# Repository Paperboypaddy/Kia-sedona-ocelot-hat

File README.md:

# Kia Sedona 2004 Ocelot Hat
The idea of this Ocelot V2 Hat design is to control the stock cruise control system in the car currently as well as adding a K Line Lin Bus tranciever to act like a ELM327 to capture car speed and other stats for openpilot.

Im using a MC33660BEFR2 chip to interface with Lin Bus K-Line over serial USART. USART isconnected to PB10 (TX) and PC5 (RX) on the Ocelot, along with Enable connected to PB1.

As for the cruise control switches and mosfets, my stock cruise control system is using 12v signals for the buttons. The series of mosfets are connected to PC10 (CCSET_INPUT) and PC11 (CCRES_INPUT). And the Stock Switches are connected to 3.3V and PC12 (CCSET_SW) and PD2 (CCRES_SW). 

I've also added a RGB status LED in place where the Black Panda would have had one.

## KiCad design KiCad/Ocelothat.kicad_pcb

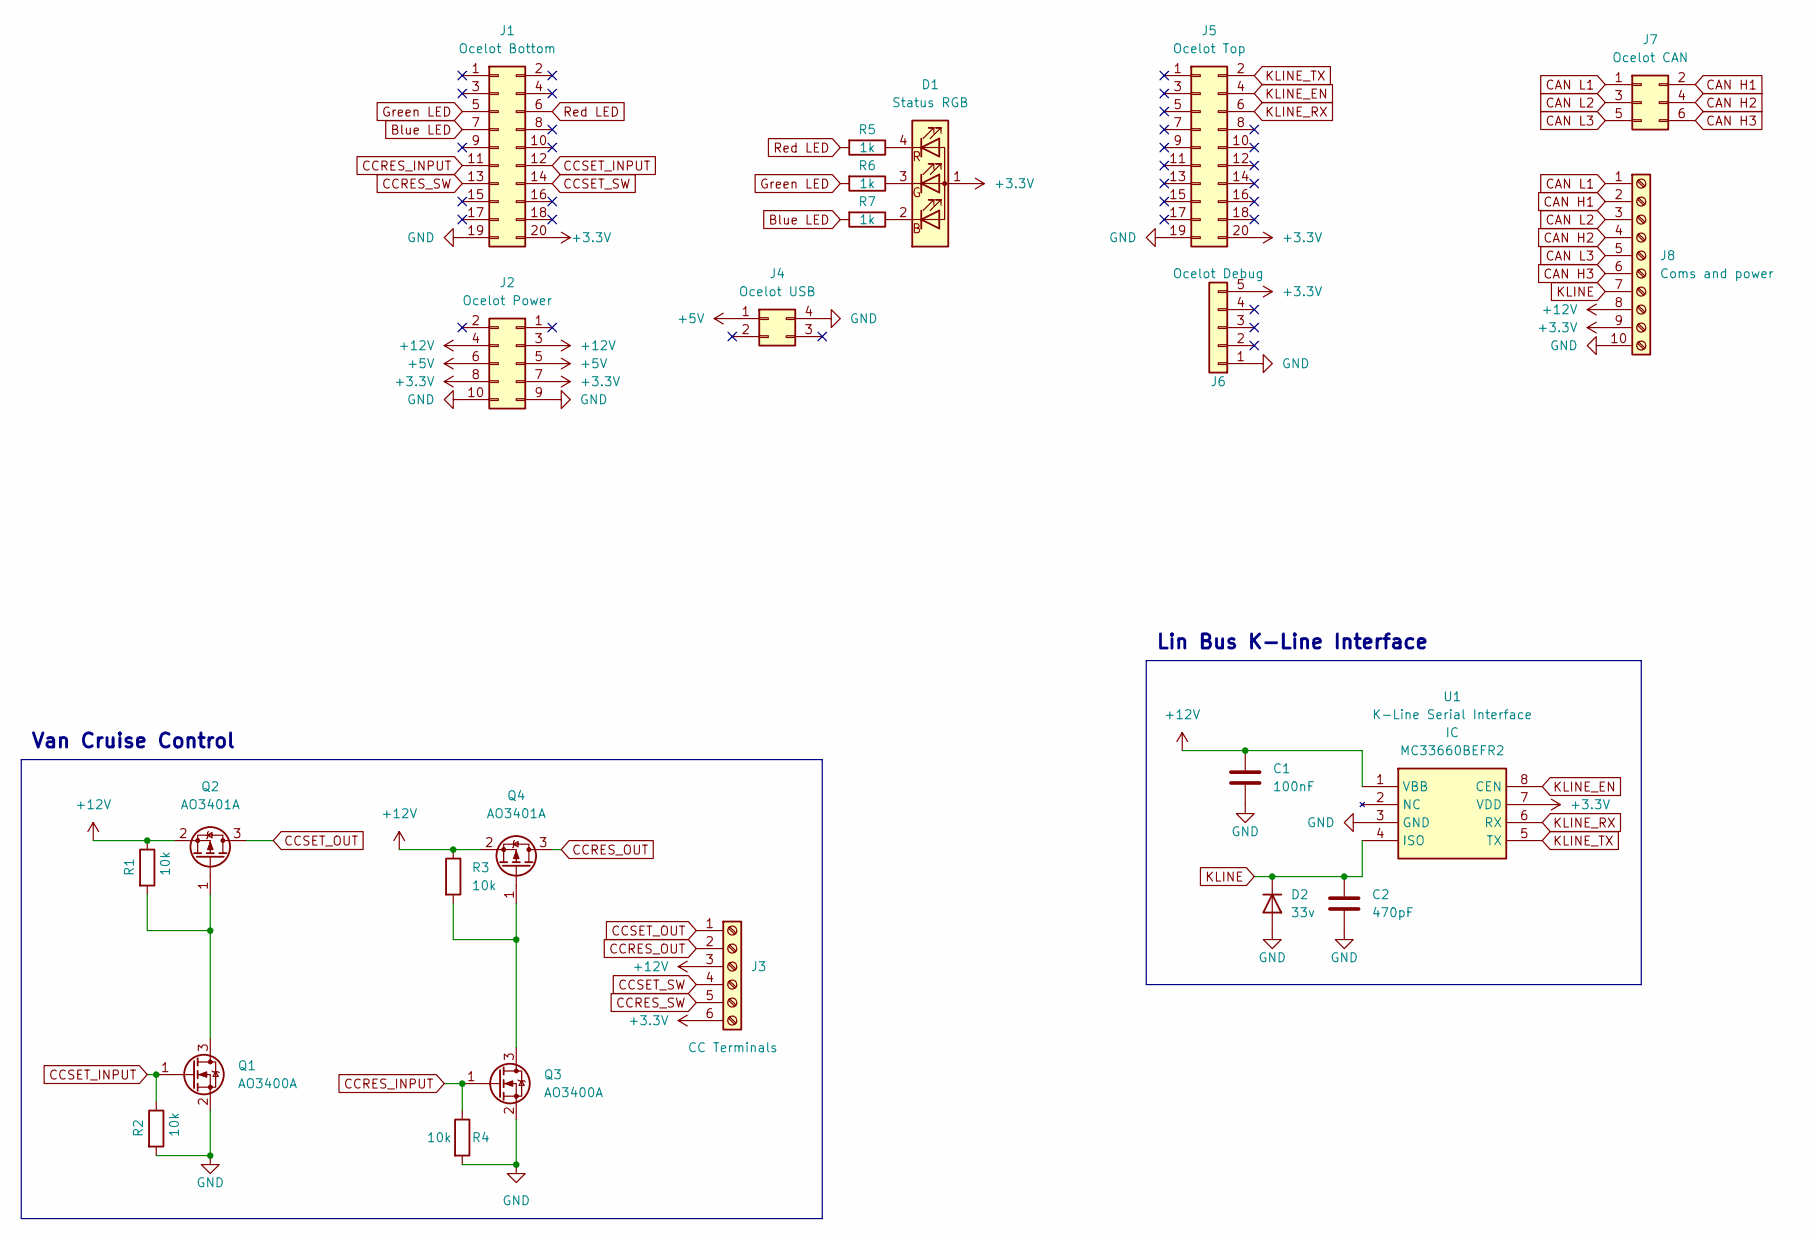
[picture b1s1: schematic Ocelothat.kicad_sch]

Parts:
C1: 100nF; C_0402_1005Metric
C2: 470pF; C_0402_1005Metric
D1: Status RGB; ASMBLTC20A335
D2: 33v; D_0402_1005Metric
J1: Ocelot Bottom; PinHeader_2x10_P2.54mm_Vertical
J2: Ocelot Power; PinHeader_2x05_P2.54mm_Vertical
J3: CC Terminals; TerminalBlock_Phoenix_MPT-0,5-6-2.54_1x06_P2.54mm_Horizontal
J4: Ocelot USB; PinHeader_2x02_P2.54mm_Vertical
J5: Ocelot Top; PinHeader_2x10_P2.54mm_Vertical
J6: Ocelot Debug; PinHeader_1x05_P2.54mm_Vertical
J7: Ocelot CAN; PinHeader_2x03_P2.54mm_Vertical
J8: Coms and power; TerminalBlock_Phoenix_MPT-0,5-10-2.54_1x10_P2.54mm_Horizont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
Q1, Q3: AO3400A; SOT-23
Q2, Q4: AO3401A; SOT-23
R1, R2, R3, R4: 10k; R_0402_1005Metric
R5, R6, R7: 1k; R_0402_1005Metric
U1: K-Line Serial Interface; SOIC127P600X175-8N; Manufacturer_Part_Number MC33660BEFR2; Mouser Part Number 841-MC33660BEFR2

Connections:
+3.3V: D1.1 (A), J1.20, J2.7, J2.8, J3.6, J5.20, J6.5, J8.9, U1.7 (VDD)
+5V: J2.5, J2.6, J4.1
+12V: C1.1, J2.3, J2.4, J3.3, J8.8, Q2.2 (S), Q4.2 (S), R1.1, R3.1, U1.1 (VBB)
Blue LED: J1.7, R7.2
CAN H1: J7.2, J8.2
CAN H2: J7.4, J8.4
CAN H3: J7.6, J8.6
CAN L1: J7.1, J8.1
CAN L2: J7.3, J8.3
CAN L3: J7.5, J8.5
CCRES_INPUT: J1.11, Q3.1 (G), R4.1
CCRES_OUT: J3.2, Q4.3 (D)
CCRES_SW: J1.13, J3.5
CCSET_INPUT: J1.12, Q1.1 (G), R2.1
CCSET_OUT: J3.1, Q2.3 (D)
CCSET_SW: J1.14, J3.4
GND: C1.2, C2.2, D2.2 (A), J1.19, J2.9, J2.10, J4.4, J5.19, J6.1, J8.10, Q1.2 (S), Q3.2 (S), R2.2, R4.2, U1.3 (GND)
Green LED: J1.5, R6.2
KLINE: C2.1, D2.1 (K), J8.7, U1.4 (ISO)
KLINE_EN: J5.4, U1.8 (CEN)
KLINE_RX: J5.6, U1.6 (RX)
KLINE_TX: J5.2, U1.5 (TX)
unnamed: D1.2 (BK), R7.1
unnamed: D1.3 (GK), R6.1
unnamed: D1.4 (RK), R5.1
unnamed: Q1.3 (D), Q2.1 (G), R1.2
unnamed: Q3.3 (D), Q4.1 (G), R3.2
Red LED: J1.6, R5.2

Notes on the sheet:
Van Cruise Control
Lin Bus K-Line Interface

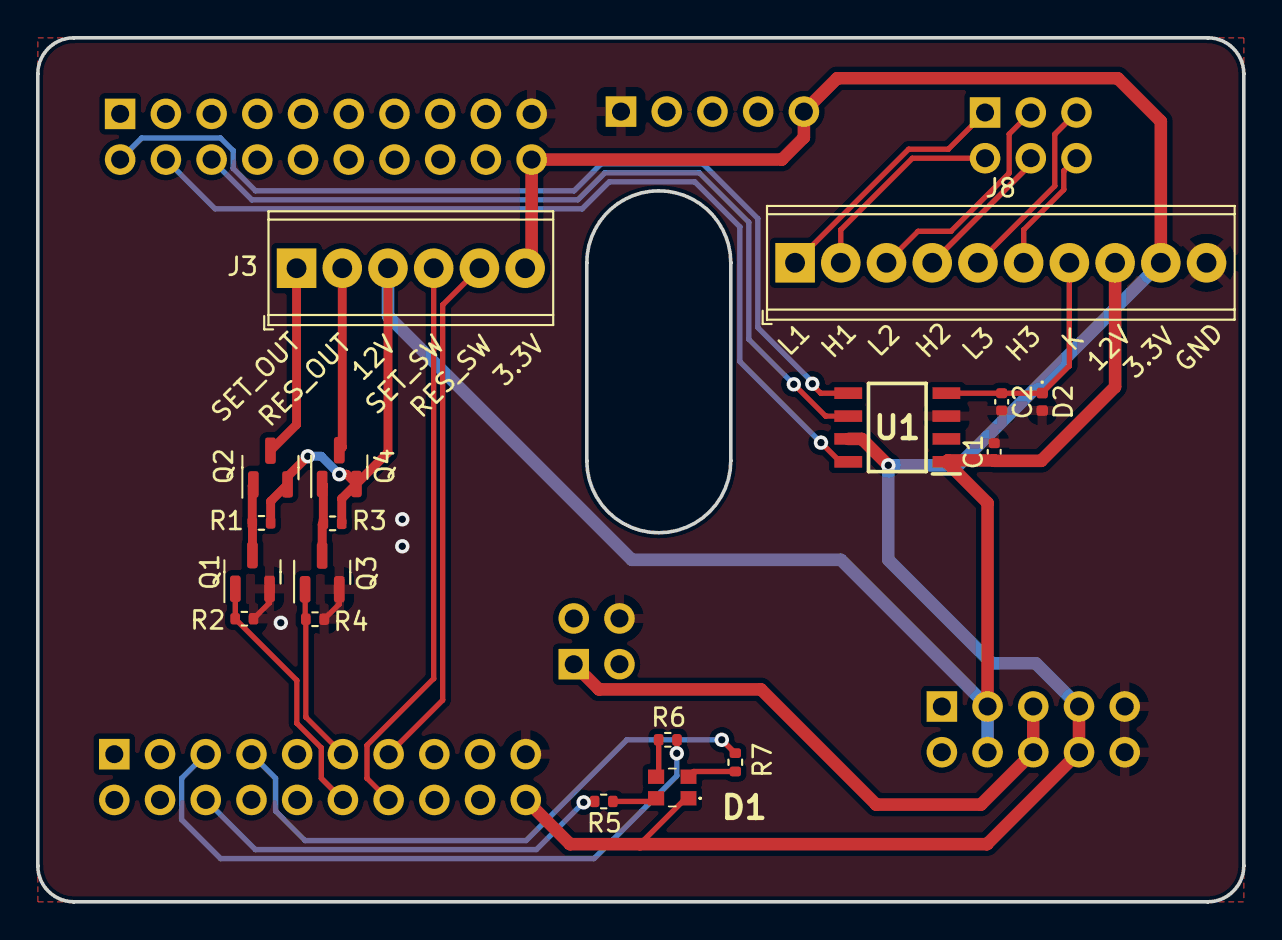
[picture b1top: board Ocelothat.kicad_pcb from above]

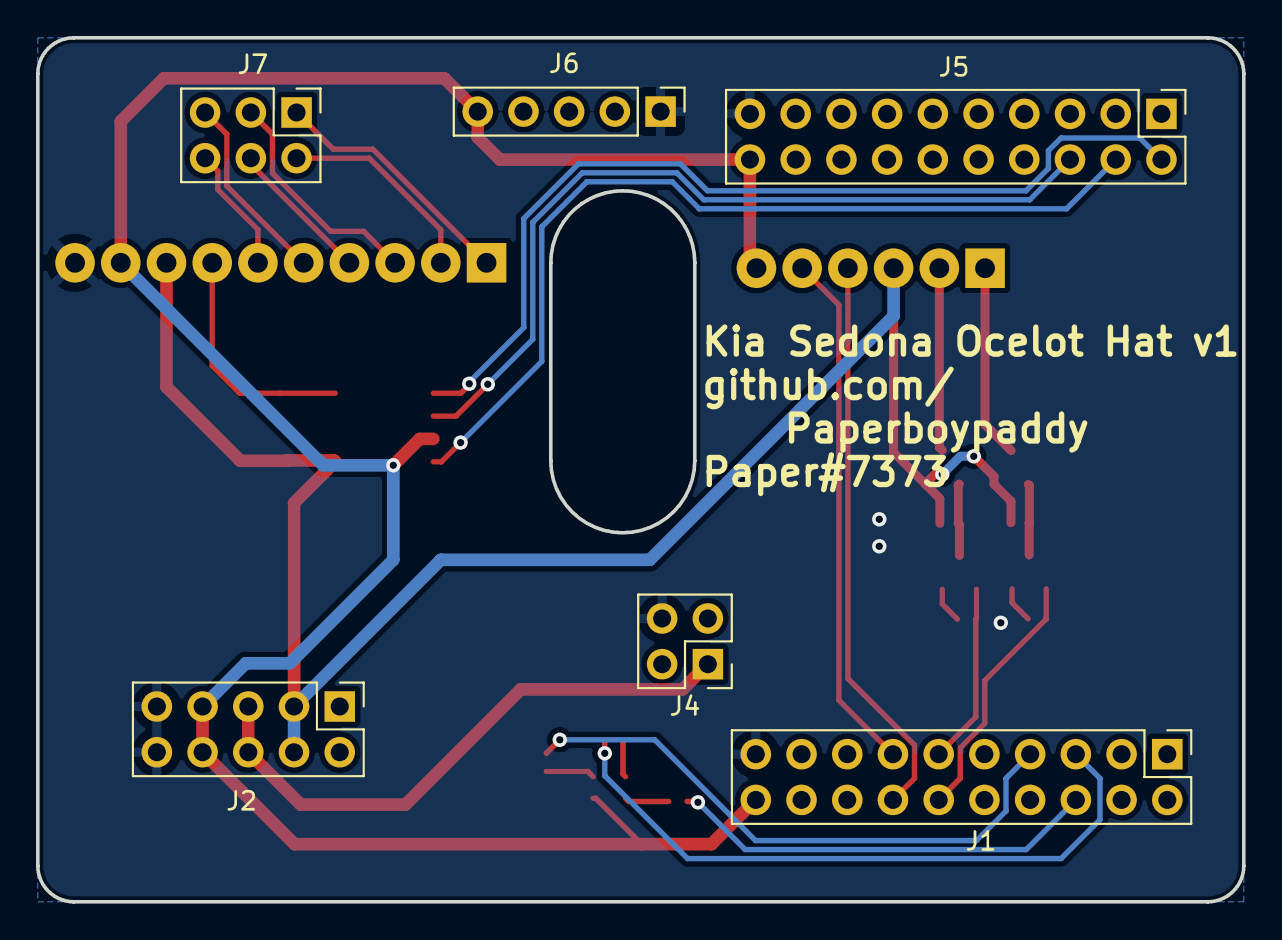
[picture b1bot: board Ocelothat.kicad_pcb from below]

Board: 2 copper layers, 67.0 x 48.0 mm, 24 parts (6 on the bottom side), 28 nets.

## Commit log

2023-04-24 Uploading KiCad Design
2023-04-24 Changed Folder name to KiCad and added images
2023-04-24 Added board Sch image
